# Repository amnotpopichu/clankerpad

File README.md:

# Clankerpad
Clankerpad is a 8 switch + rotary encoder bluetooth macropad built on the ZMK supported Xiao nRF52840. Also my first big electronics project and custom pcb. I made this project because I am brand new to electronics, so I felt that this would be a nice fun challenging twist on a already really cool project.

# Firmware
https://github.com/amnotpopichu/clankerpad-zmk-config
Final link above, I did half of it, half of it was claude. I dont know how subrepos work, see my most recent journal entry, i hope this is ok.

# Images

# Disclaimer/Notes
I am importing most of this journal from a previous google doc that I had running for it. Times to do things may look crazy but i swear im not commiting fraud im just a bit stupid and this is my first project. If verb tense look weird, sorry, I am rewriting some entries to make it more clear (my old ones kinda sucked).

Images also may have disrepncies not logged, ie quick 15 minute rerouting, or small changes here and there to fix bugs, but I felt those wern't big enough to add a journal entry for.

There is a discrepncy between the created date in the yaml and the github repo. I have been working on this in a google doc for long before the repo. (I would be happy to send over proof if needed.)

Also links in my BOM may link to multi packs. I funded this project oustide of hackclub, so it may not reflect how many were actaully used. Some links are not the exact ones, as some parts were sourced in kit (aka just the black switch).

There are some questionable price choices, but this project was kinda rushed so I paid extra for shipping.

If there is some really odd journal entries, ie spending 3 hours on pcb design, sorry i didnt lapse i genuinely didnt know what that was until recently, i swear im not tryna fraud im just stupid lol

tldr: im not tryna commit fraud im js stupid and brand new :(

# Credits
Big thank you to everyone in HC that offered advice with my questions, and super huge thank you to [@JBlitzar](https://github.com/JBlitzar) and [@hekinav](https://github.com/hekinav)

|Name                       |Link                                                                                     |Quantity|Total cost                              |
|---------------------------|-----------------------------------------------------------------------------------------|--------|----------------------------------------|
|EC11                       |https://www.amazon.com/QSYZAIL-Rotary-Encoder-Compatible-Arduino/dp/B0G528SYTB/          |1       |8.87                                    |
|Xiao BLE                   |https://www.amazon.com/Seeed-Studio-XIAO-nRF52840-Sense/dp/B0DJ6NZVJT?th=1               |1       |35.99                                   |
|Generic 3 pin switch (SPDT)|https://www.amazon.com/Position-Vertical-Silver-Black-Available-Electronic/dp/B0DR2J8FY3/|1       |0 (self sourced)                        |
|pcb                        |N/A                                                                                      |1       |3.2                                     |
|tax                        |N/A                                                                                      |1       |0.31                                    |
|customs                    |N/A                                                                                      |1       |1.12                                    |
|Shipping                   |N/A                                                                                      |1       |32.88                                   |
|3d printed case            |N/A                                                                                      |1       |0 (self sourced)                        |
|Glorious Panda Switches    |https://www.amazon.com/Glorious-Panda-Switch-LUBED-GLO-SWT-HPANDA-LUBED/dp/B096DF64NS/   |8       |0 (taken from some that I already owned)|
|gmk samurai keycaps        |N/A                                                                                      |8       |0 (taken from some that I already owned)|
|jst connector for lipo     |https://www.amazon.com/dp/B013JRWCBU                                                     |1       |6.99                                    |
|lipo battery               |https://www.amazon.com/dp/B0867KDMY7                                                     |1       |18.99                                   |

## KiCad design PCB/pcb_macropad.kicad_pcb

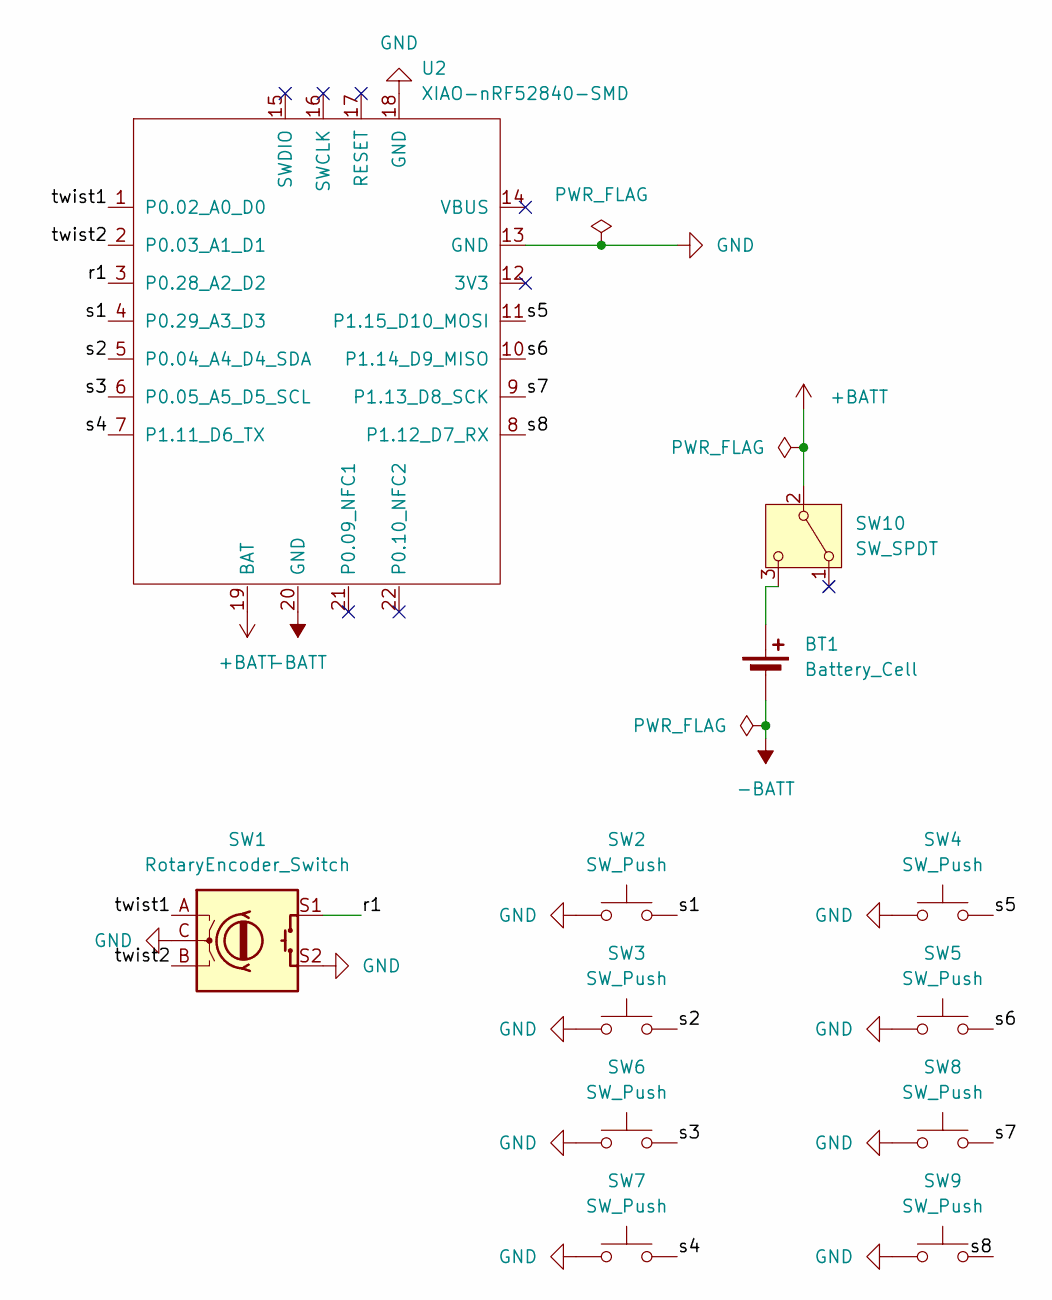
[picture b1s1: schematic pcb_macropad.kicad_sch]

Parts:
BT1: Battery_Cell; PinHeader_1x02_P2.54mm_Vertical
SW1: RotaryEncoder_Switch; RotaryEncoder_Alps_EC11E-Switch_Vertical_H20mm
SW2, SW3, SW4, SW5, SW6, SW7, SW8, SW9: SW_Push; SW_Cherry_MX_1.00u_PCB
SW10: SW_SPDT; PinHeader_1x03_P2.54mm_Vertical
U2: XIAO-nRF52840-SMD

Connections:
+BATT: SW10.2 (B), U2.19 (BAT)
-BATT: BT1.2 (-), U2.20 (GND); also elsewhere on the board
/r1: SW1.S1, U2.3 (P0.28_A2_D2)
/s1: SW2.2, U2.4 (P0.29_A3_D3)
/s2: SW3.2, U2.5 (P0.04_A4_D4_SDA)
/s3: SW6.2, U2.6 (P0.05_A5_D5_SCL)
/s4: SW7.2, U2.7 (P1.11_D6_TX)
/s5: SW4.2, U2.11 (P1.15_D10_MOSI)
/s6: SW5.2, U2.10 (P1.14_D9_MISO)
/s7: SW8.2, U2.9 (P1.13_D8_SCK)
/s8: SW9.2, U2.8 (P1.12_D7_RX)
/twist1: SW1.A, U2.1 (P0.02_A0_D0)
/twist2: SW1.B, U2.2 (P0.03_A1_D1)
GND: SW1.C, SW1.S2, SW2.1, SW3.1, SW4.1, SW5.1, SW6.1, SW7.1, SW8.1, SW9.1, U2.13 (GND), U2.18 (GND)
unnamed 14: BT1.1 (+), SW10.3 (C); also elsewhere on the board

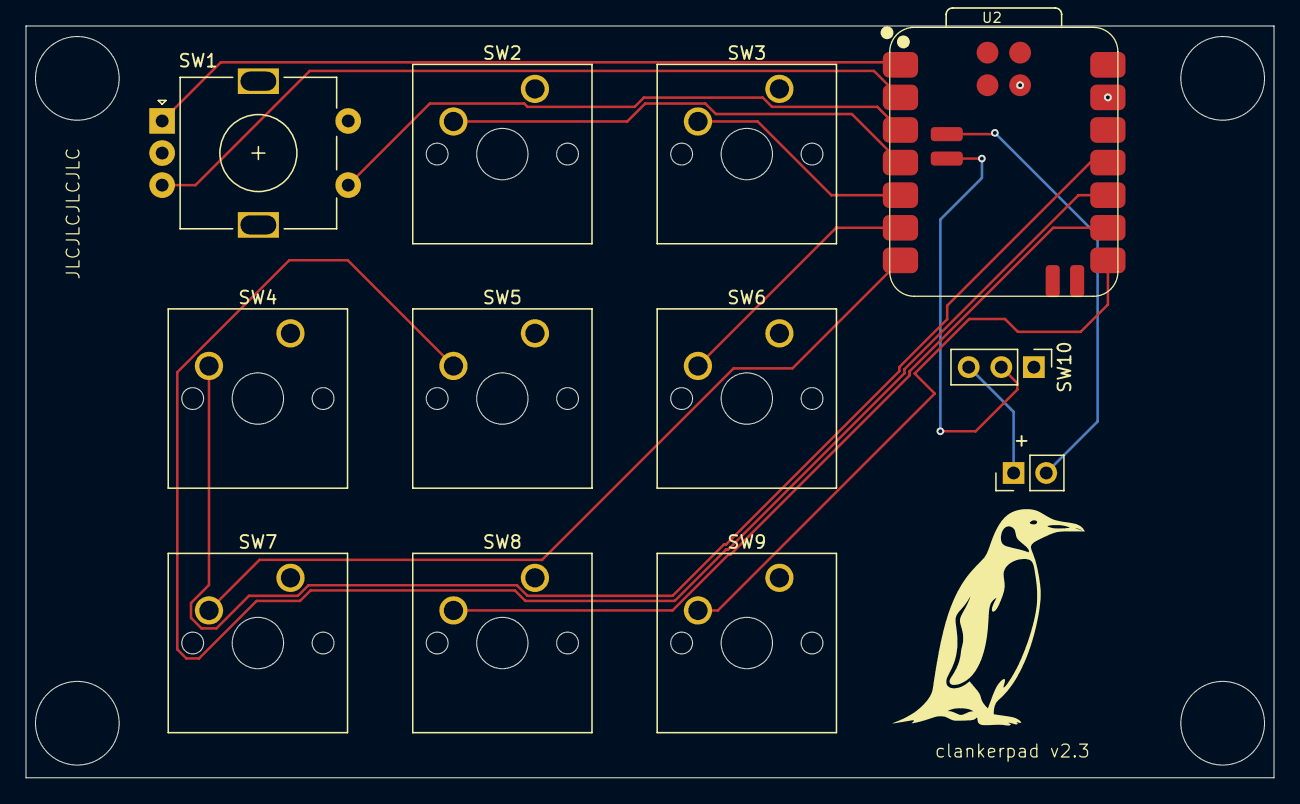
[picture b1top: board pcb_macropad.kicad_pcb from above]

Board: 2 copper layers, 97.3 x 58.6 mm, 12 parts (0 on the bottom side), 15 nets.

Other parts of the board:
+: Battery_Cell; PinHeader_1x02_P2.54mm_Vertical

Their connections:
-BATT: +.2 (-); also elsewhere on the board
unnamed 14: +.1 (+); also elsewhere on the board

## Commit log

2026-05-15 transcribed first two journal entries
2026-05-15 figured out total didnt mean total in total but total for that entry
2026-05-15 updated journal to may 5th
2026-05-15 updated journal
2026-05-15 YAY EVERYTHING IS UP TO DATE
2026-05-15 added pcb files
2026-05-15 restructured files
2026-05-15 may 15
2026-05-22 journal
2026-05-22 journal fr cus i cant use git
2026-05-29 YAY journals
2026-05-29 fixed images
2026-05-30 fixed it fr this tiem
2026-06-02 added firmware v1 (claude)
2026-06-04 firmware
2026-06-04 fix ts
2026-06-04 pls work
2026-06-04 fially done
2026-06-04 bro link work
2026-06-04 i hope im done
2026-06-08 revisions
2026-06-09 bro im dubm
